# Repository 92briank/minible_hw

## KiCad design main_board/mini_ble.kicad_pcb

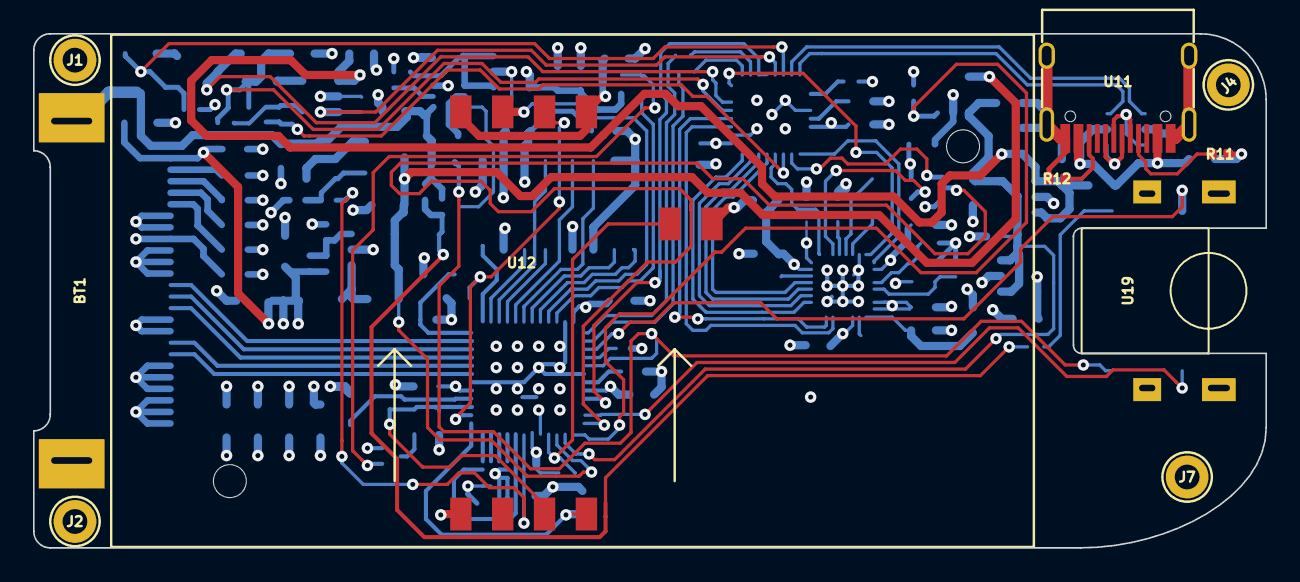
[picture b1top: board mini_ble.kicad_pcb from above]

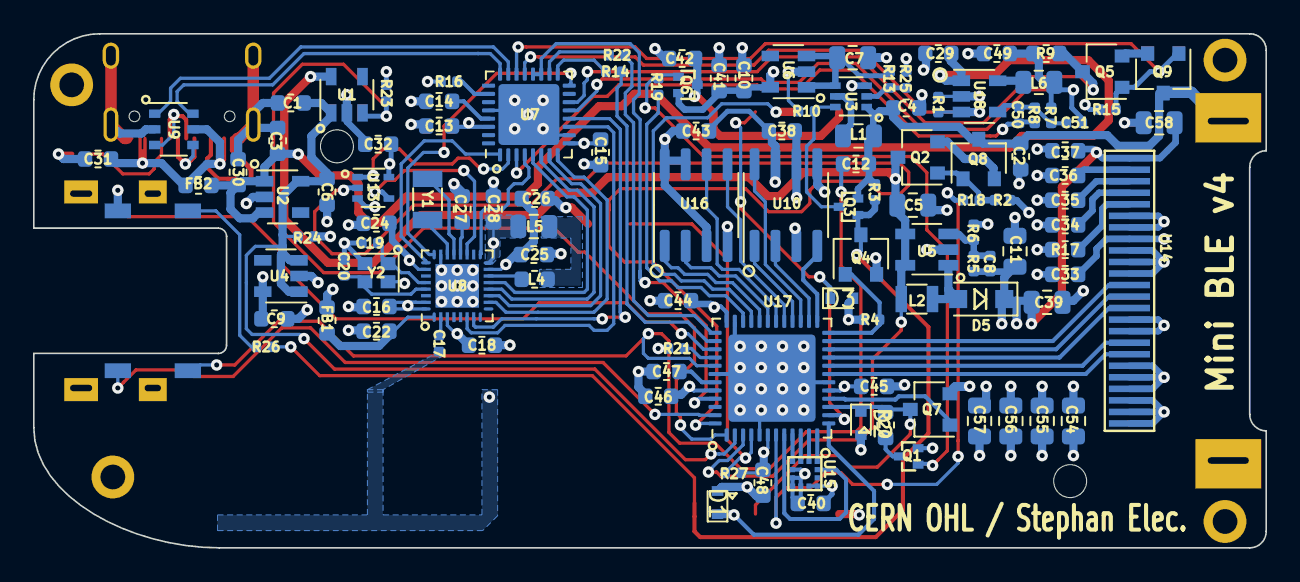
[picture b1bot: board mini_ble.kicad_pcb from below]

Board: 4 copper layers, 74.8 x 31.2 mm, 127 parts (117 on the bottom side), 101 nets.

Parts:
BT1: NiMH; BAT_TWOTHIRD_AAA
C1, C2, C3, C6, C9, C10, C14, C18, C27, C30, C47: 1uF/25V; C_0603_1608Metric
C4, C12, C49: 10uF/6.3V; C_0603_1608Metric
C5, C7, C11, C39, C54, C55, C56, C57, C58: 10uF/16V; C_0805_2012Metric
C8: 200p; C_0402_1005Metric
C13, C15, C16, C22, C24, C31, C32, C38, C40, C41, C42, C43, C44, C45, C46, C48: 100nF; C_0603_1608Metric
C17: 10pF; C_0402_1005Metric
C19, C20: 5.6pF; C_0402_1005Metric
C25: 10nF; C_0603_1608Metric
C26: 2.2uF; C_0603_1608Metric
C28, C29, C33, C34, C35, C36, C37: 4.7uF; C_0603_1608Metric
C50, C51: C; C_0402_1005Metric
D1, D2, D3: Zener 3.3V; D_SOD-523
D5: MBR230S1; D_SOD-123F
FB1: 120R,100Mhz,200mA; R_0603_1608Metric
FB2: FER; R_0603_1608Metric
J1, J2, J4, J7: FIX_M1.4
L1, L5, L6: 4.7uH; L_0805_2012Metric
L2: 680nH; L_0806
L4: 9.1nH; L_0603_1608Metric
Q1, Q3, Q6: SI1013X; SC89
Q2, Q4, Q5, Q7, Q8, Q9: DMN1019USN; SC-59
R1, R2, R5, R15, R23, R24, R25: 100k; R_0402_1005Metric
R3, R4, R10, R27: 1M; R_0402_1005Metric
R6: 17k8; R_0402_1005Metric
R7: 54k9; R_0402_1005Metric
R8: 20k; R_0402_1005Metric
R9: 1; R_0603_1608Metric
R11, R12: 5.1k; R_0402_1005Metric
R13: 536k; R_0402_1005Metric
R14, R22, R26: 100; R_0402_1005Metric
R16, R18, R19, R21: 10k; R_0402_1005Metric
R17: 620k; R_0603_1608Metric
R20: 2k2; R_0603_1608Metric
U1, U4, U6: MAX40200; SOT-23-5
U2: MIC5504; SOT-23-5
U3: TPS61220; SOT-363_SC-70-6
U5: LT1613; TSOT-23-5
U7: ATSAMD21E15B; QFN-32-1EP_5x5mm_P0.5mm_EP3.7x3.7mm
U8: ATBTLC1000; QFN-32-1EP_4x4mm_Pitch0.4mm
U9: IP4234CZ6,125; TSOP-6_1.65x3.05mm_P0.95mm
U10: AT45DB081E; SOIC-8_3.9x4.9mm_P1.27mm
U11: USBC_Receptacle; USB_C_Receptacle_GT-USB-7010
U12: CON_SMARTCARD; CON_SMARTCARD_CLONE_91-90473-003A
U13: NC7SZ08P5X; SOT-353_SC-70-5
U14: OLED_M01084; SCREEN_M01084
U15: LIS2HH12; LGA-12
U16: W25Q16; SOIC-8_3.9x4.9mm_P1.27mm
U17: SAMD21G18A-MU; QFN-48-1EP_7x7mm_P0.5mm_EP5.3x5.3mm
U18: LM3670; SOT-23-5
U19: WHEEL_SRBE210200; SRBE210200
Y1: 32.768Khz; Crystal_SMD_3215-2Pin_3.2x1.5mm
Y2: 26Mhz; Crystal_SMD_2016-4Pin_2.0x1.6mm

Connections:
+1V2: C16.1, C18.1, C28.2, FB1.2, L5.2, U8.3, U8.16, U8.31, U8.32
+1V5: BT1.1, C2.1, C4.1, C12.1, L1.1, Q3.2, Q8.3, Q9.3, R3.1, U3.1
+3V3: C9.1, C10.1, C13.1, C15.1, C24.1, C25.1, C26.1, C32.1, C33.1, C38.1, C40.1, C41.1, C43.1, C44.1, C45.1, C46.1, C48.1, Q1.2, Q6.2, R16.1, R21.2, R27.2, U4.5, U6.5, U7.9, U7.30, U8.15, U8.26, U10.3, U10.5, U10.6, U13.5, U14.8, U15.9, U15.10, U16.3, U16.7, U16.8, U17.6, U17.17, U17.36, U17.44
+5V: C3.1, C29.1, C30.1, FB2.2, U2.1, U2.3, U18.1
+8V: C8.1, C11.1, C37.1, C39.1, C54.1, C55.1, C56.1, C57.1, C58.1, D5.1, R5.1, U14.1
/Bluetooth and USB/BLE_CHIP_EN: U7.2, U13.1
/Bluetooth and USB/BLE_CHIP_EN_AND: U8.19, U13.4
/Bluetooth and USB/BLE_CHIP_SEC_EN: U13.2, U17.48
/Bluetooth and USB/BLE_CTS_UART1: U7.7, U8.11
/Bluetooth and USB/BLE_HOST_WAKEUP: U7.4, U8.17
/Bluetooth and USB/BLE_RTC_CLKOUT: U7.1, U8.25
/Bluetooth and USB/BLE_RTS_UART1: U7.8, U8.10
/Bluetooth and USB/BLE_RX_UART0: U7.11, U8.6
/Bluetooth and USB/BLE_RX_UART1: U7.5, U8.13
/Bluetooth and USB/BLE_TX_UART0: U7.12, U8.7
/Bluetooth and USB/BLE_TX_UART1: U7.6, U8.12
/Bluetooth and USB/BLE_WAKE: U7.16, U8.24
/Bluetooth and USB/CHARGE_EN: R1.2, U7.21, U18.3
/Bluetooth and USB/CURSENSE_HIGH: C49.1, C51.2, L6.1, R7.2, R9.1, U7.13
/Bluetooth and USB/CURSENSE_LOW: Q5.3, R9.2, U7.14
/Bluetooth and USB/MOS_CHARGE: Q5.1, Q9.1, R15.2, U7.22
/Bluetooth and USB/NO_COMMS: U7.19, U7.20, U17.45
/Bluetooth and USB/USB_D+: U7.24, U9.6
/Bluetooth and USB/USB_D-: U7.23, U9.1
/Bluetooth and USB/VFBBIAS: C50.1, R8.1, U7.3
/Bluetooth and USB/nRST: R16.2, U7.26
/Main MCU & OLED/3V3_USB: C1.1, C6.1, R24.1, U1.1, U2.5, U4.1, U4.3, U17.2
/Main MCU & OLED/ACC_INT: U15.12, U17.8
/Main MCU & OLED/ACC_MISO: U15.3, U17.10
/Main MCU & OLED/ACC_MOSI: U15.4, U17.9
/Main MCU & OLED/ACC_SCK: U15.1, U17.12
/Main MCU & OLED/ACC_SS: U15.2, U17.11
/Main MCU & OLED/AUX_RX: R22.1, U17.37
/Main MCU & OLED/AUX_TX: R14.1, U17.38
/Main MCU & OLED/DATA_FLASH_MISO: U16.2, U17.31
/Main MCU & OLED/DATA_FLASH_MOSI: U16.5, U17.29
/Main MCU & OLED/DATA_FLASH_SCK: U16.6, U17.30
/Main MCU & OLED/DATA_FLASH_nCS: U16.1, U17.32
/Main MCU & OLED/DB_FLASH_MISO: U10.8, U17.27
/Main MCU & OLED/DB_FLASH_MOSI: U10.1, U17.28
/Main MCU & OLED/DB_FLASH_SCK: U10.2, U17.26
/Main MCU & OLED/DB_FLASH_nCS: U10.4, U17.25
/Main MCU & OLED/ENC_A: U17.39, U19.A
/Main MCU & OLED/ENC_B: U17.47, U19.B
/Main MCU & OLED/OLED_DATA: U14.18, U17.19
/Main MCU & OLED/OLED_DnR: U14.14, U17.21
/Main MCU & OLED/OLED_SCK: U14.17, U17.20
/Main MCU & OLED/OLED_nCS: U14.12, U17.23
/Main MCU & OLED/OLED_nRES: U14.13, U17.22
/Main MCU & OLED/SMC_DET: R27.1, U12.S1, U17.4
/Main MCU & OLED/SMC_MISO: D2.1, Q7.3, R20.2, U12.C7, U17.15
/Main MCU & OLED/SMC_MOSI: Q7.1, U17.16
/Main MCU & OLED/SMC_PGM: D1.1, U12.C8, U17.13
/Main MCU & OLED/SMC_POW_nEN: R19.1, U17.34
/Main MCU & OLED/SMC_RST: U12.C2, U17.33
/Main MCU & OLED/SMC_SCK: D3.1, U12.C3, U17.14
/Main MCU & OLED/SWDET_ENABLE: Q4.1, R4.2, U17.24
/Main MCU & OLED/SWITCH_HIGH: C12.2, U17.41, U19.PUSH
/Main MCU & OLED/SWITCH_LOW: R26.2, U19.COM
/Main MCU & OLED/VOLED_1V2_EN: R18.1, U17.7
/Main MCU & OLED/VOLED_3V3_EN: R23.2, U1.3, U17.1
/Main MCU & OLED/VOLED_DC_IN: C5.1, L2.1, Q2.3, U1.5, U5.4, U5.5, U17.3
/Main MCU & OLED/~RST: R21.1, U17.40
GND: BT1.2, C1.2, C2.2, C3.2, C4.2, C5.2, C6.2, C7.2, C9.2, C10.2, C11.2, C13.2, C14.2, C15.2, C16.2, C17.2, C18.2, C19.1, C20.2, C22.2, C24.2, C25.2, C26.2, C27.2, C28.1, C29.2, C30.2, C31.2, C32.2, C33.2, C34.2, C35.2, C36.2, C37.2, C38.2, C39.2, C40.2, C41.2, C42.2, C43.2, C44.2, C45.2, C46.2, C47.2, C48.2, C49.2, C54.2, C55.2, C56.2, C57.2, C58.2, D1.2, D2.2, D3.2, J1.1, J2.1, J4.1, J7.1, Q4.2, Q7.2, R1.1, R2.2, R4.1, R6.2, R10.1, R11.2, R12.2, R15.1, R17.2, R23.1, R24.2, R25.2, U1.2, U2.2, U3.3, U4.2, U5.2, U6.2, U7.10, U7.28, U7.33, U8.23, U8.33, U9.2, U10.7, U11.A1, U11.A12, U11.B1, U11.B12, U11.S1, U12.C5, U12.S2, U13.3, U14.6, U14.7, U14.9, U14.10, U14.11, U14.15, U14.16, U14.19, U14.20, U14.21, U14.22, U14.23, U14.24, U15.5, U15.6, U15.7, U15.8, U16.4, U17.5, U17.18, U17.35, U17.42, U17.49, U18.2, U19.FIX1, U19.FIX2, Y2.2, Y2.4
unnamed: C7.1, R13.1, U3.4, U6.1, U6.3
unnamed: C8.2, R5.2, R6.1, U5.3
unnamed: C14.1, U7.29
unnamed: C17.1, U8.2
unnamed: C19.2, U8.28, Y2.1
unnamed: C20.1, U8.29, Y2.3
unnamed: C22.1, FB1.1, U8.1
unnamed: C27.1, U8.20
unnamed: C31.1, FB2.1, U9.5, U11.A4, U11.A9, U11.B4, U11.B9
unnamed: C34.1, U14.4
unnamed: C35.1, U14.3
unnamed: C36.1, U14.2
unnamed: C42.1, Q6.3, U12.C1, U12.C4
unnamed: C47.1, U17.43
unnamed: C50.2, C51.1, R7.1, R8.2, U18.4
unnamed: D5.2, L2.2, U5.1
unnamed: L1.2, U3.5
unnamed: L4.1, U8.14
unnamed: L4.2, L5.1
unnamed: L6.2, U18.5
unnamed: Q1.1, Q6.1, R19.2
unnamed: Q1.3, R20.1
unnamed: Q2.1, Q8.1, R2.1, R18.2
unnamed: Q2.2, Q8.2
unnamed: Q3.1, Q4.3, R3.2, R26.1
unnamed: Q3.3, R10.2, U3.6
unnamed: Q5.2, Q9.2
unnamed: R11.1, U11.A5
unnamed: R12.1, U11.B5
unnamed: R13.2, R25.1, U3.2
unnamed: R14.2, U7.17
unnamed: R17.1, U14.5
unnamed: R22.2, U7.18
unnamed: U8.21, Y1.1
unnamed: U8.22, Y1.2
unnamed: U9.4, U11.A6, U11.B6
unnamed: U9.3, U11.A7, U11.B7

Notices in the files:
main_board/mini_ble.kicad_pcb:
CERN OHL / Stephan Elec.
